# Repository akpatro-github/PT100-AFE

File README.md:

# PT100-AFE
Analog Front-End for the PT100 temperature sensor inside the HIMA temperature chamber.

||
|:--:|
|*Figure 1: Block Diagram of PT-100*|

# PT-100 Temperature vs. Resistance Data

[Click Here](https://github.com/akpatro-github/PT100-AFE/blob/main/Python/pt100-datasheet.csv) to get the PT-100 Temperature vs. Resistance Data.

# Analog Front-End (AFE) Architecture

## 1. Design Summary
The Design requirements are as follows:
- Supply voltage: 5V
- RTD Temperature range: -40℃ to 151℃
- RTD Resistance range: 84.27Ω to 157.69Ω
- Output Range: 0V to 5V

## 2. Theory of operation

 - Figure 2 shows the schematic of the RTD amplifier for minimum and maximum output conditions. Note that this circuit was designed for a -40℃ to 151℃ RTD temperature range.
 - At -40℃ the RTD resistance is 84.27Ω and the voltage across it is 8.427mV (VRTD = (100μA)(84.27Ω)). 
 - Notice that Rtrim develops a voltage drop that opposes the RTD drop. The drop across Rtrim is used to shift amplifiers input differential voltage to a minimum level. 
 - The output is the differential input multiplied by the gain (Vout = 659.67 x 227μV = 0.1497V). 
 - At 151℃ the RTD resistance is 157.69Ω and the voltage across it is 15.769mV (VRTD = (100μA)(157.69Ω)). 
 - This produces a differential input of 7.569mV and an output voltage of 4.9930V (Vout = 659.67 x 7.569mV = 4.9930V).

||
|:--:|
|*Fig 2: RTD Amplifier with minimum and maximum output condition*|

### 2.1. **Lead Resistance cancelation (3 wire RTD)**
	
 - Figure 3 below shows the three wire RTD configuration can be used to cancel lead resistance.Note that the resistance in each lead must be equal to cancel the error. Also, the two current sources in the REF200 need to be equal. 
 - 
 - Notice that the voltage developed on the two top leads of the RTD are equal and opposite polarity so that the amplifiers input is only from the RTD voltage. 
 - At 151C, the RTD drop is 15.679mV and the leads each have 0.02mV. Notice that the 0.02mV drops cancel. 
 - Finally, notice that the voltage on the 3rd lead (0.04mV) creates a small shift in the common mode voltage. However, the INA826 has a rail to rail common mode range, so it can accept common mode voltages near ground.

||
|:--:|
|*Figure 3: Schematic of AFE*|

### 2.2 Noise Calculation
#### Resistror Noise
For Analysis purpose, Rwire = 20Ω,
		     Temperature = 45℃(318k), 
		     B.W. = 30KHz

||
|:--:|
|*Figure 4: Resistance Noise *|

Resistance Noise  | Value (nV/Hz^0.5) |
 ------------ | :-----------: | 
Vnr1      |          1.34 |
Vnr2       |   2.1  | 
Vnr3       |   0.6  | 

#### Current Noise

From the datasheet of INA826 current noise = 

||
|:--:|
|*Figure 5: Current Noise *|

Current Noise  | Value (pV/Hz^0.5) |
 ------------ | :-----------: | 
Vnc1      |          1.8 |
Vnc2       |   1.02  | 
Vnc3       |   0.4  | 

#### Voltage Noise

#### Total Noise for a Bandwidth of 30KHz

 ### 2.3 Selecting Gain and Offset Resistor

- Calculate the required Gain (ΔVout/ΔVin)

- Choose standard resistors to assure that the actual gain is equal to or less than the calculated gain. From INA826 data sheet we get the gain equation as:

- Calculate a value of R3 based on the minimum output voltage and the gain
R3 = 82Ω (standard value)

### 2.4 External Low Pass Filter
- Given that when G = 1000, BandWidth = 6KHz (From Data sheet of INA826)
- In this operation G = 659.67, So B.W. = 9.1KHz
- calculating the value of Rf and Cf

From this equation
Rf = 75Ω &
Cf = 0.22uF

## 3. PCB Design
This PCB layout was designed using [Autodesk Eagle](https://www.autodesk.in/products/eagle/overview). For the components we have used [SparkFun Eagle Libraries](https://github.com/sparkfun/SparkFun-Eagle-Libraries). The footprints of the ICs(INA 826, Ref200) can be downloaded from the [Ultra Librarian](https://www.ultralibrarian.com/).

### 3.1. Electrical Schematic

||
|:--:|
|*Figure 4:Electrical Schematic *|

### 3.1. PCB Layout

#### PCB Guidelines

 - Fine-Tuning Your Component Placement
 - Placing Your Power, Ground & Signal Traces
 - Keeping Things Separate
 - Placing the decoupling capacitors nearer to the IC pins
 - Checking Your Layout Against Your PCB Design Rules

||
|:--:|
|*Figure 5: PCB Top - Red*|

||
|:--:|
|*Figure 6: PCB Bottom - Blue*|

### 3.2. Component Selection

[Click Here](https://github.com/akpatro-github/PT100-AFE/blob/main/PCB/bill_of_comp.csv) to get the bill of components.

# Analog Discovery 2
## Specification
- 14 Bit ADC
- Voltage Range: -25V to 25V

## Operation
### Calculating Bit of operation we need 
- Required voltage range: 0-5V
- So, we need to use 11 Bit ADC (Voltage Range: 0-6.25V)

### LSB Calculation
- Temperature Range: -40℃ to 151℃
- No of Samples 192, we have taken 256(2^8) no. of samples
- So we can represent 1℃ using 8bit
- *For 11 Bit of operation LSB = 0.125℃*

## Analysis using Python
### Resistance Vs Temperature Plot

||
|:--:|
|*Fig 7:Resistance Vs Temperature*|

### AFE o/p Voltage Vs Temperature Plot

||
|:--:|
|*Fig 8:AFE o/p Voltage Vs Temperature*|

### Code Vs Temperature Plot

||
|:--:|
|*Fig 9:Code Vs Temperature*|

### Error Vs Temperature Plot

||
|:--:|
|*Fig 10:Error Vs Temperature*|

[Click Here](https://github.com/akpatro-github/PT100-AFE/blob/main/Python/pt100.py) to get the python code.

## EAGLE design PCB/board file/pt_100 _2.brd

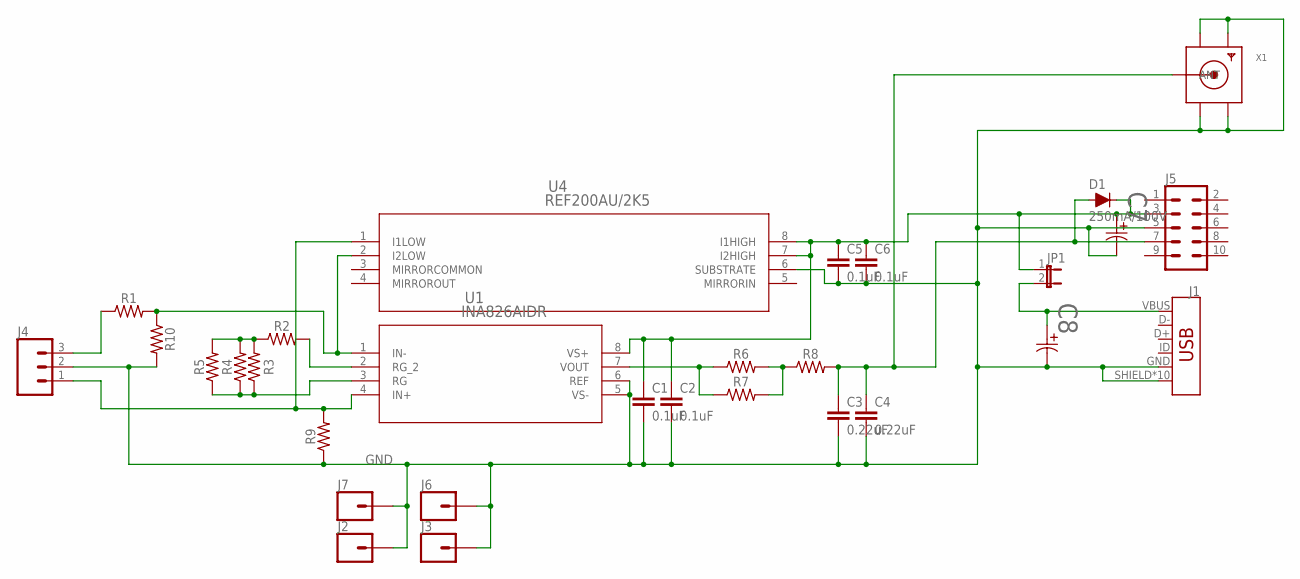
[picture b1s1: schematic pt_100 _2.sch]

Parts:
C1, C2, C5, C6: 0.1uF; 0402
C3, C4: 0.22uF; 0402
C7, C8: T491D106K025AT; CAPMP7.6X4.3_3.1N_KEM
D1: 250mA/100V; SOD-323
J1: USB_MICRO-B_HALF_PTH_MILL; USB-MICROB-PTH-MILL
J2, J3, J6, J7: CONN_01; 1X01
J4: CONN_03-SCREW-5MM; SCREWTERMINAL-5MM-3
J5: CONN_05X2SHD_LOCK; 2X5-SHROUDED_LOCK
JP1: JUMPER-2PTH; 1X02
R1: 82; 0402
R2, R8: 0; 0402
R3, R4, R5, R6: 75; 0402
R7, R9, R10: 1KOHM-0402-1/16W-1%; 0402
U1: INA826AIDR; D8
U4: REF200AU/2K5; D8
X1: SMACONNECTOR_EDGE; SMA_EDGELAUNCH

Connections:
GND: C1.2, C2.2, C3.2, C4.2, C5.2, C6.2, C7.2, C8.2, J1.GND, J1.SHIELD, J1.SHIELD2 (SHIELD), J1.SHIELD3 (SHIELD), J1.SHIELD4 (SHIELD), J1.SHIELD5 (SHIELD), J1.SHIELD6 (SHIELD), J1.SHIELD7 (SHIELD), J1.SHIELD8 (SHIELD), J1.SHIELD9 (SHIELD), J1.SHIELD10 (SHIELD), J2.1, J3.1, J4.2, J5.5, J6.1, J7.1, R9.1, R10.2, U1.5 (VS-), U1.6 (REF), U4.6 (SUBSTRATE), X1.GND@1 (GND4), X1.GND@2 (GND3), X1.GND@3 (GND2), X1.GND@4 (GND1)
unnamed: C8.1, J1.VBUS, JP1.2
unnamed: J4.3, R1.1
unnamed: R1.2, R10.1, U1.1 (IN-), U4.2 (I2LOW)
unnamed: R6.2, R7.2, R8.1
unnamed: R6.1, R7.1, U1.7 (VOUT)
unnamed: R2.2, U1.2 (RG_2)
unnamed: R3.1, R4.1, R5.1, U1.3 (RG)
unnamed: J4.1, R9.2, U1.4 (IN+), U4.1 (I1LOW)
unnamed: C3.1, C4.1, D1.A, J5.7, R8.2, X1.P (ANT)
unnamed: R2.1, R3.2, R4.2, R5.2
unnamed: C1.1, C2.1, C5.1, C6.1, C7.1, D1.C, J5.3, JP1.1, U1.8 (VS+), U4.7 (I2HIGH), U4.8 (I1HIGH)

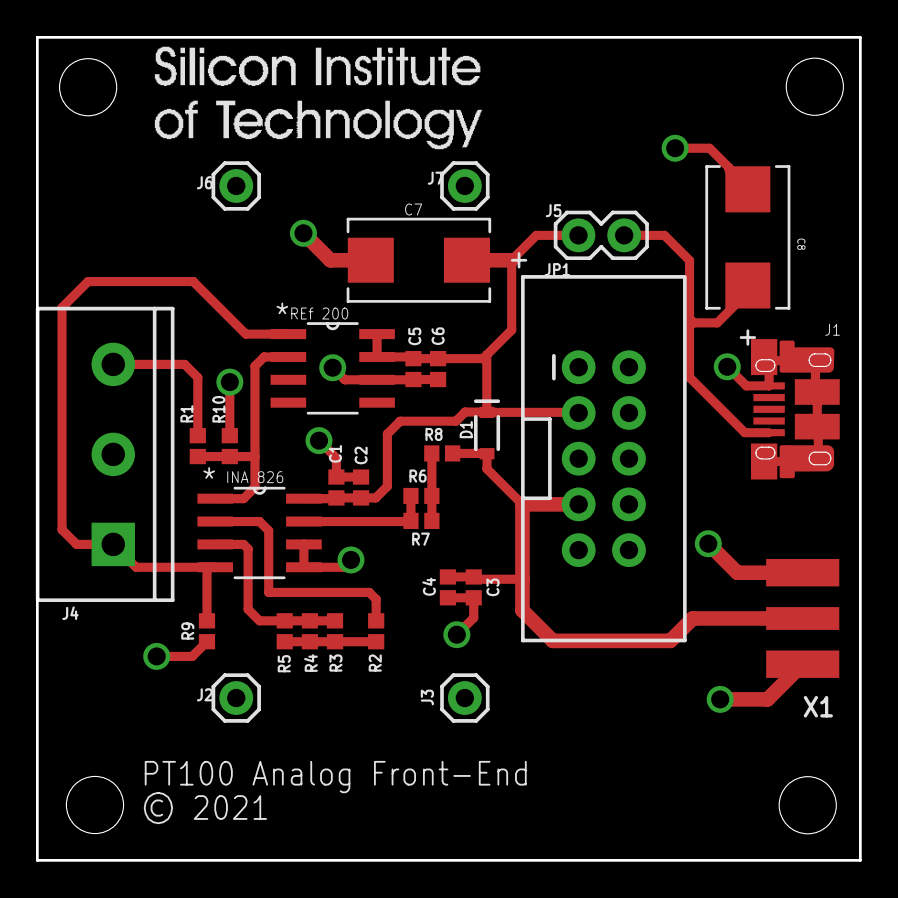
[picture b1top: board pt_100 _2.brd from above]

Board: 2 copper layers, 45.7 x 45.7 mm, 30 parts (0 on the bottom side), 12 nets.

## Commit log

2021-02-22 block diagram added
2021-02-22 deleted
2021-02-23 Added gbr files
2021-02-24 python program added
2021-02-24 bill of comp added
2021-02-26 board file added
2021-03-19 block added
2021-03-19 schematic added
2021-03-19 noise

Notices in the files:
PCB/board file/pt_100 _2.brd:
© 2021
parts and their libraries:
SparkFun-Retired: Licensing: Creative Commons ShareAlike 4.0 International - https://creativecommons.org/licenses/by-sa/4.0
